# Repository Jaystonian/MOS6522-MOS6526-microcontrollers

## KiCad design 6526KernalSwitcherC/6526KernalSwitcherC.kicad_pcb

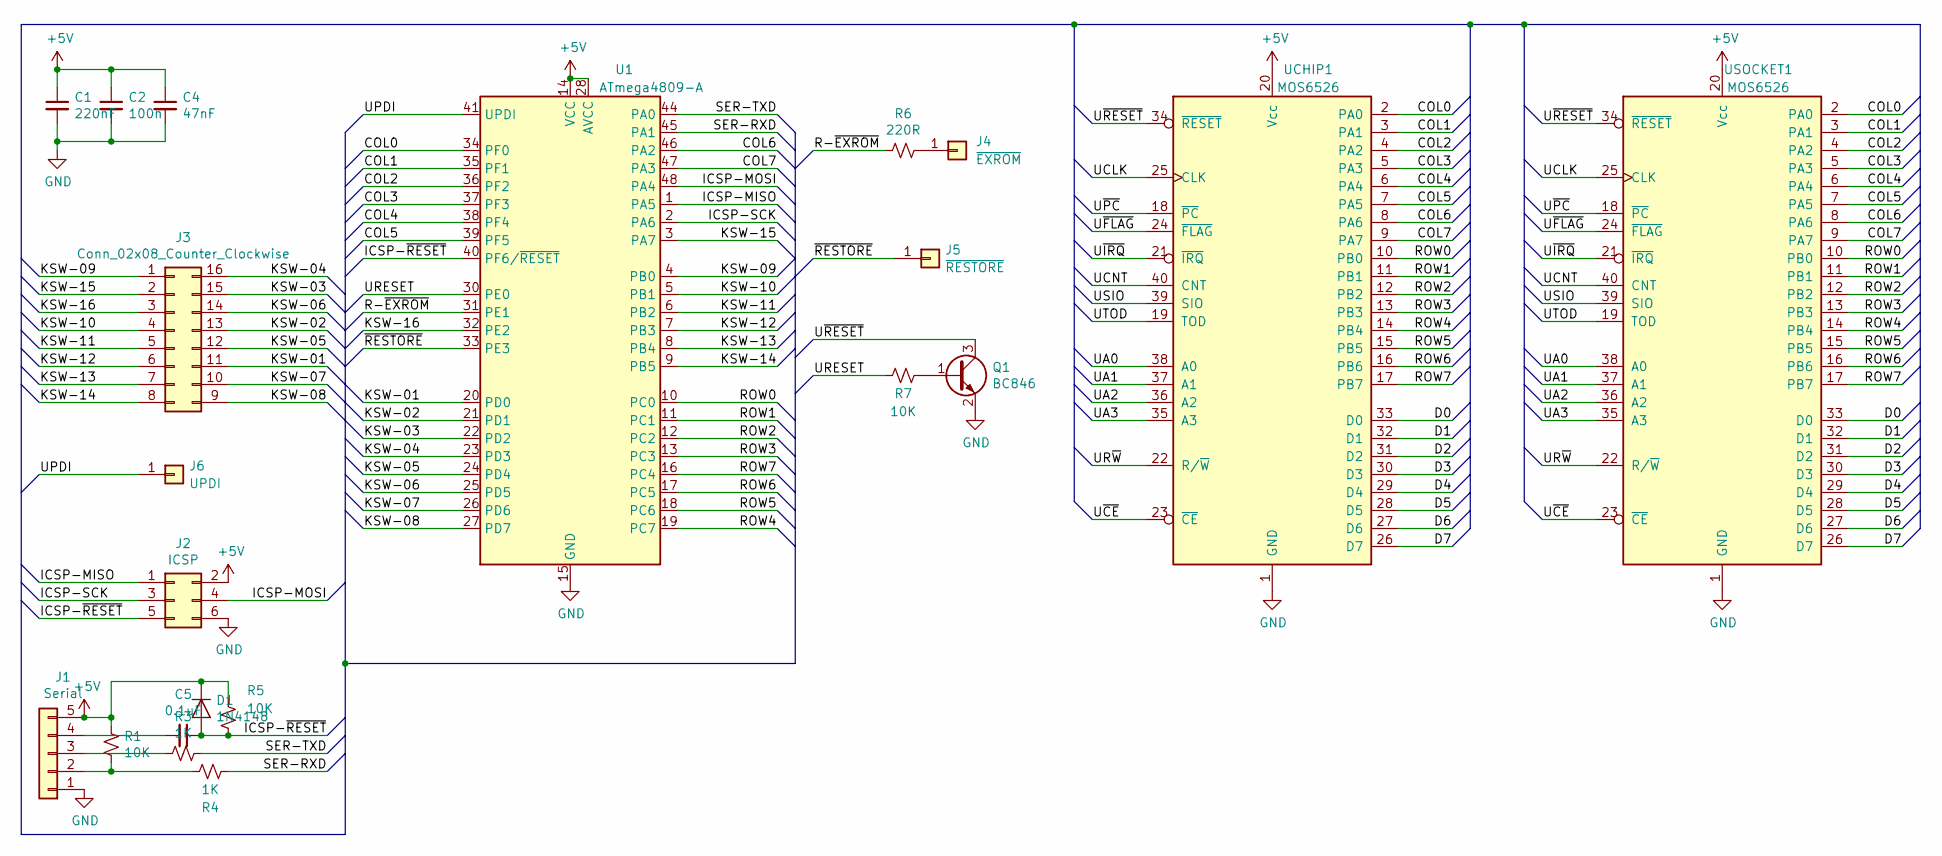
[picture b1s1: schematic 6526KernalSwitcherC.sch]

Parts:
C1: 220nF; C_0805_2012Metric_Pad1.15x1.40mm_HandSolder
C2: 100n; C_0805_2012Metric_Pad1.15x1.40mm_HandSolder
C4: 47nF; C_0805_2012Metric_Pad1.15x1.40mm_HandSolder
C5: 0.1uF; C_0805_2012Metric_Pad1.15x1.40mm_HandSolder
D1: 1N4148; D_MiniMELF
J1: Serial; PinHeader_1x05_P1.27mm_Vertical
J2: ICSP; PinHeader_2x03_P1.27mm_Vertical_SMD
J3: Conn_02x08_Counter_Clockwise; PinHeader_2x08_P2.00mm_Vertical
J4: ~EXROM; PinHeader_1x01_P2.54mm_Vertical
J5: ~RESTORE; PinHeader_1x01_P2.54mm_Vertical
J6: UPDI; PinHeader_1x01_P2.54mm_Vertical
Q1: BC846; SOT-23
R1, R5, R7: 10K; R_0805_2012Metric_Pad1.15x1.40mm_HandSolder
R3, R4: 1K; R_0805_2012Metric_Pad1.15x1.40mm_HandSolder
R6: 220R; R_0805_2012Metric_Pad1.15x1.40mm_HandSolder
U1: ATmega4809-A; TQFP-48_7x7mm_P0.5mm
UCHIP1: MOS6526; DIP-40_W15.24mm
USOCKET1: MOS6526; DIP-40_W15.24mm

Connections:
+5V: C1.1, C2.1, C4.1, D1.1 (K), J1.5, J2.2, R1.1, R5.1, U1.14 (VCC), U1.28 (AVCC), U1.42 (VCC), UCHIP1.20 (Vcc), USOCKET1.20 (Vcc)
/COL0: U1.34 (PF0), UCHIP1.2 (PA0), USOCKET1.2 (PA0)
/COL1: U1.35 (PF1), UCHIP1.3 (PA1), USOCKET1.3 (PA1)
/COL2: U1.36 (PF2), UCHIP1.4 (PA2), USOCKET1.4 (PA2)
/COL3: U1.37 (PF3), UCHIP1.5 (PA3), USOCKET1.5 (PA3)
/COL4: U1.38 (PF4), UCHIP1.6 (PA4), USOCKET1.6 (PA4)
/COL5: U1.39 (PF5), UCHIP1.7 (PA5), USOCKET1.7 (PA5)
/COL6: U1.46 (PA2), UCHIP1.8 (PA6), USOCKET1.8 (PA6)
/COL7: U1.47 (PA3), UCHIP1.9 (PA7), USOCKET1.9 (PA7)
/D0: UCHIP1.33 (D0), USOCKET1.33 (D0)
/D1: UCHIP1.32 (D1), USOCKET1.32 (D1)
/D2: UCHIP1.31 (D2), USOCKET1.31 (D2)
/D3: UCHIP1.30 (D3), USOCKET1.30 (D3)
/D4: UCHIP1.29 (D4), USOCKET1.29 (D4)
/D5: UCHIP1.28 (D5), USOCKET1.28 (D5)
/D6: UCHIP1.27 (D6), USOCKET1.27 (D6)
/D7: UCHIP1.26 (D7), USOCKET1.26 (D7)
/ICSP-MISO: J2.1, U1.1 (PA5)
/ICSP-MOSI: J2.4, U1.48 (PA4)
/ICSP-SCK: J2.3, U1.2 (PA6)
/ICSP-~RESET: C5.1, D1.2 (A), J2.5, R5.2, U1.40 (PF6/~RESET)
/KSW-01: J3.11, U1.20 (PD0)
/KSW-02: J3.13, U1.21 (PD1)
/KSW-03: J3.15, U1.22 (PD2)
/KSW-04: J3.16, U1.23 (PD3)
/KSW-05: J3.12, U1.24 (PD4)
/KSW-06: J3.14, U1.25 (PD5)
/KSW-07: J3.10, U1.26 (PD6)
/KSW-08: J3.9, U1.27 (PD7)
/KSW-09: J3.1, U1.4 (PB0)
/KSW-10: J3.4, U1.5 (PB1)
/KSW-11: J3.5, U1.6 (PB2)
/KSW-12: J3.6, U1.7 (PB3)
/KSW-13: J3.7, U1.8 (PB4)
/KSW-14: J3.8, U1.9 (PB5)
/KSW-15: J3.2, U1.3 (PA7)
/KSW-16: J3.3, U1.32 (PE2)
/R-~EXROM: R6.2, U1.31 (PE1)
/ROW0: U1.10 (PC0), UCHIP1.10 (PB0), USOCKET1.10 (PB0)
/ROW1: U1.11 (PC1), UCHIP1.11 (PB1), USOCKET1.11 (PB1)
/ROW2: U1.12 (PC2), UCHIP1.12 (PB2), USOCKET1.12 (PB2)
/ROW3: U1.13 (PC3), UCHIP1.13 (PB3), USOCKET1.13 (PB3)
/ROW4: U1.19 (PC7), UCHIP1.14 (PB4), USOCKET1.14 (PB4)
/ROW5: U1.18 (PC6), UCHIP1.15 (PB5), USOCKET1.15 (PB5)
/ROW6: U1.17 (PC5), UCHIP1.16 (PB6), USOCKET1.16 (PB6)
/ROW7: U1.16 (PC4), UCHIP1.17 (PB7), USOCKET1.17 (PB7)
/SER-RXD: R4.1, U1.45 (PA1)
/SER-TXD: R3.1, U1.44 (PA0)
/UA0: UCHIP1.38 (A0), USOCKET1.38 (A0)
/UA1: UCHIP1.37 (A1), USOCKET1.37 (A1)
/UA2: UCHIP1.36 (A2), USOCKET1.36 (A2)
/UA3: UCHIP1.35 (A3), USOCKET1.35 (A3)
/UCLK: UCHIP1.25 (CLK), USOCKET1.25 (CLK)
/UCNT: UCHIP1.40 (CNT), USOCKET1.40 (CNT)
/UPDI: J6.1, U1.41 (UPDI)
/URESET: R7.2, U1.30 (PE0)
/UR~W: UCHIP1.22 (R/~W~), USOCKET1.22 (R/~W~)
/USIO: UCHIP1.39 (SIO), USOCKET1.39 (SIO)
/UTOD: UCHIP1.19 (TOD), USOCKET1.19 (TOD)
/U~CE: UCHIP1.23 (~CE~), USOCKET1.23 (~CE~)
/U~FLAG: UCHIP1.24 (~FLAG~), USOCKET1.24 (~FLAG~)
/U~IRQ: UCHIP1.21 (~IRQ~), USOCKET1.21 (~IRQ~)
/U~PC: UCHIP1.18 (~PC~), USOCKET1.18 (~PC~)
/U~RESET: Q1.3 (C), UCHIP1.34 (~RESET~), USOCKET1.34 (~RESET~)
/~RESTORE: J5.1, U1.33 (PE3)
GND: C1.2, C2.2, C4.2, J1.1, J2.6, Q1.2 (E), U1.15 (GND), U1.29 (GND), U1.43 (GND), UCHIP1.1 (GND), USOCKET1.1 (GND)
unnamed: C5.2, J1.4
unnamed: J1.2, R1.2, R4.2
unnamed: J1.3, R3.2
unnamed: J4.1, R6.1
unnamed: Q1.1 (B), R7.1

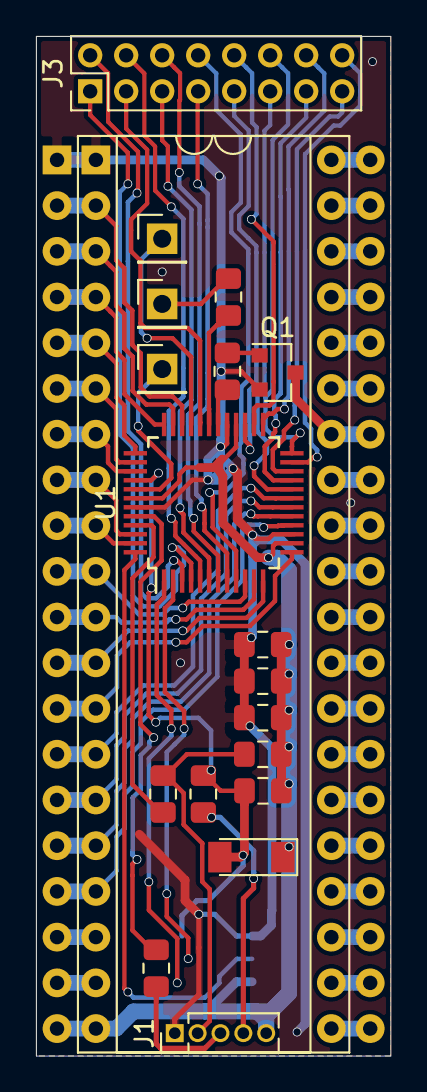
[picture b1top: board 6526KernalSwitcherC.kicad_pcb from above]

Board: 2 copper layers, 19.7 x 56.6 mm, 21 parts (1 on the bottom side), 71 nets.

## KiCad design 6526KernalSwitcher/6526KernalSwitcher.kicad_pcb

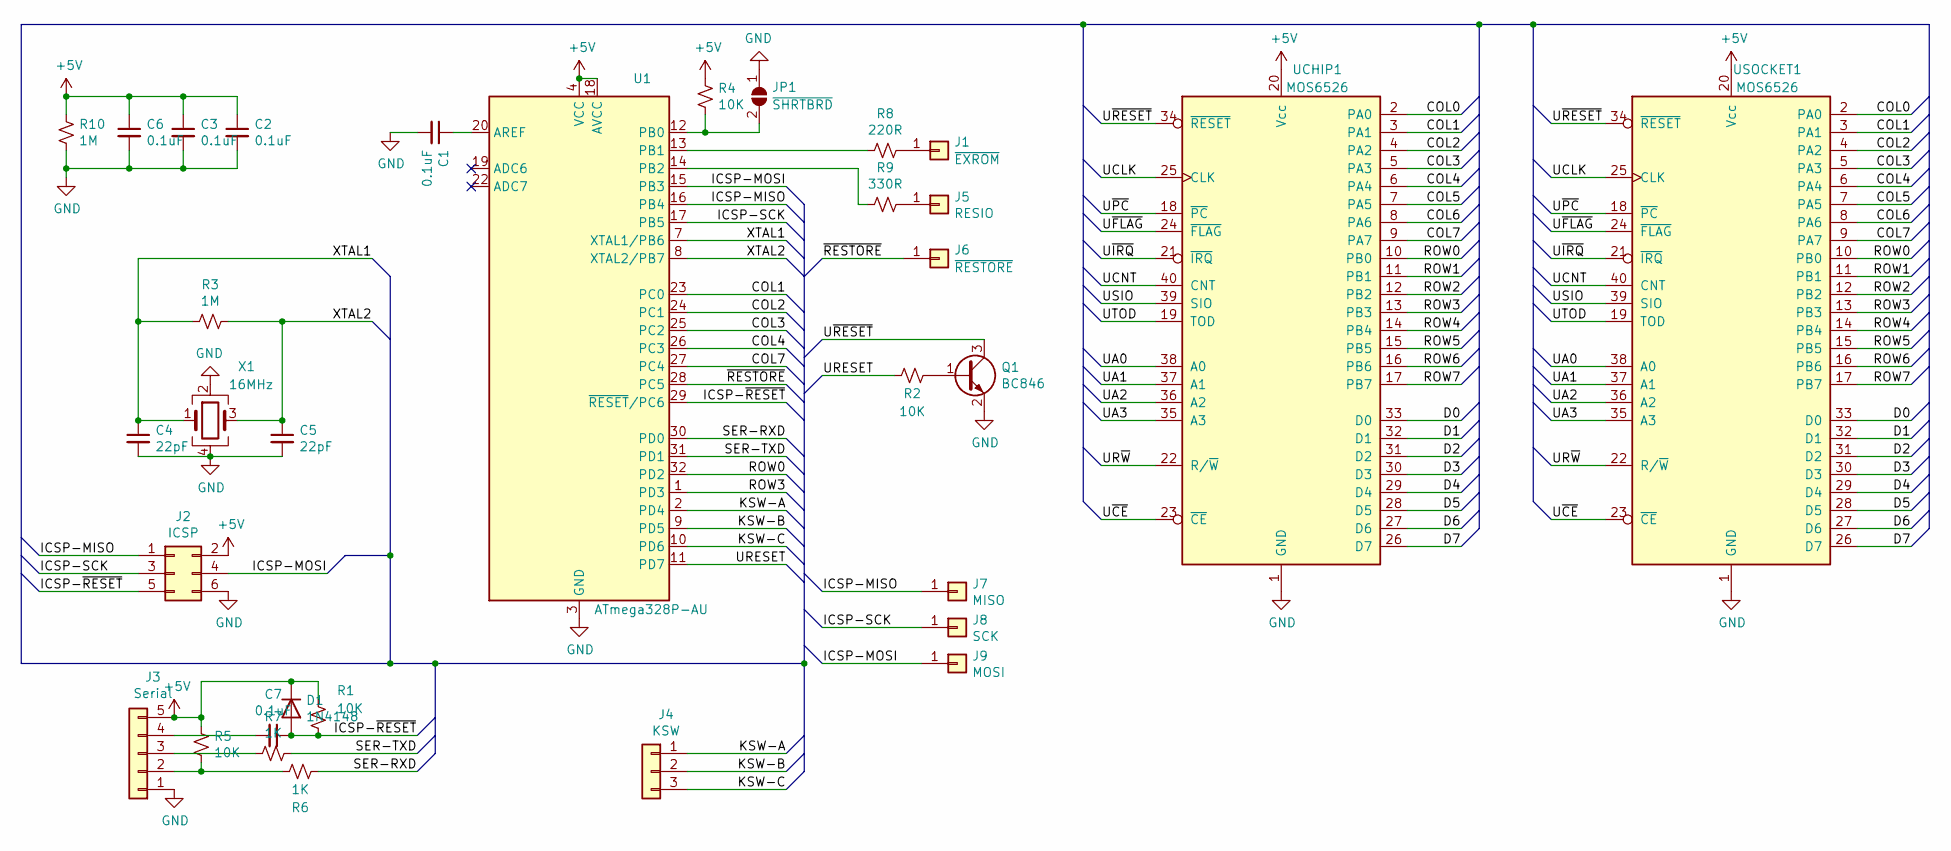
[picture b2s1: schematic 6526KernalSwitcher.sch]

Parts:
C1, C2, C3, C6, C7: 0.1uF; C_0805_2012Metric_Pad1.15x1.40mm_HandSolder
C4, C5: 22pF; C_0805_2012Metric_Pad1.15x1.40mm_HandSolder
D1: 1N4148; D_MiniMELF
J1: ~EXROM; PinHeader_1x01_P2.54mm_Vertical
J2: ICSP; PinHeader_2x03_P2.54mm_Vertical
J3: Serial; PinHeader_1x05_P2.54mm_Vertical
J4: KSW; PinHeader_1x03_P2.54mm_Vertical
J5: RESIO; PinHeader_1x01_P2.54mm_Vertical
J6: ~RESTORE; PinHeader_1x01_P2.54mm_Vertical
J7: MISO; SolderPad
J8: SCK; SolderPad
J9: MOSI; SolderPad
JP1: ~SHRTBRD; SolderJumper-2_P1.3mm_Open_RoundedPad1.0x1.5mm
Q1: BC846; SOT-23
R1, R2, R4, R5: 10K; R_0805_2012Metric_Pad1.15x1.40mm_HandSolder
R3, R10: 1M; R_0805_2012Metric_Pad1.15x1.40mm_HandSolder
R6, R7: 1K; R_0805_2012Metric_Pad1.15x1.40mm_HandSolder
R8: 220R; R_0805_2012Metric_Pad1.15x1.40mm_HandSolder
R9: 330R; R_0805_2012Metric_Pad1.15x1.40mm_HandSolder
U1: ATmega328P-AU; TQFP-32_7x7mm_P0.8mm
UCHIP1: MOS6526; DIP-40_W15.24mm
USOCKET1: MOS6526; DIP-40_W15.24mm
X1: 16MHz; Crystal_SMD_2016-4Pin_2.0x1.6mm

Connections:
+5V: C2.1, C3.1, C6.1, D1.1 (K), J2.2, J3.5, R1.1, R4.1, R5.1, R10.1, U1.4 (VCC), U1.6 (VCC), U1.18 (AVCC), UCHIP1.20 (Vcc), USOCKET1.20 (Vcc)
/COL0: UCHIP1.2 (PA0), USOCKET1.2 (PA0)
/COL1: U1.23 (PC0), UCHIP1.3 (PA1), USOCKET1.3 (PA1)
/COL2: U1.24 (PC1), UCHIP1.4 (PA2), USOCKET1.4 (PA2)
/COL3: U1.25 (PC2), UCHIP1.5 (PA3), USOCKET1.5 (PA3)
/COL4: U1.26 (PC3), UCHIP1.6 (PA4), USOCKET1.6 (PA4)
/COL5: UCHIP1.7 (PA5), USOCKET1.7 (PA5)
/COL6: UCHIP1.8 (PA6), USOCKET1.8 (PA6)
/COL7: U1.27 (PC4), UCHIP1.9 (PA7), USOCKET1.9 (PA7)
/D0: UCHIP1.33 (D0), USOCKET1.33 (D0)
/D1: UCHIP1.32 (D1), USOCKET1.32 (D1)
/D2: UCHIP1.31 (D2), USOCKET1.31 (D2)
/D3: UCHIP1.30 (D3), USOCKET1.30 (D3)
/D4: UCHIP1.29 (D4), USOCKET1.29 (D4)
/D5: UCHIP1.28 (D5), USOCKET1.28 (D5)
/D6: UCHIP1.27 (D6), USOCKET1.27 (D6)
/D7: UCHIP1.26 (D7), USOCKET1.26 (D7)
/ICSP-MISO: J2.1, J7.1, U1.16 (PB4)
/ICSP-MOSI: J2.4, J9.1, U1.15 (PB3)
/ICSP-SCK: J2.3, J8.1, U1.17 (PB5)
/ICSP-~RESET: C7.1, D1.2 (A), J2.5, R1.2, U1.29 (~RESET~/PC6)
/KSW-A: J4.1, U1.2 (PD4)
/KSW-B: J4.2, U1.9 (PD5)
/KSW-C: J4.3, U1.10 (PD6)
/ROW0: U1.32 (PD2), UCHIP1.10 (PB0), USOCKET1.10 (PB0)
/ROW1: UCHIP1.11 (PB1), USOCKET1.11 (PB1)
/ROW2: UCHIP1.12 (PB2), USOCKET1.12 (PB2)
/ROW3: U1.1 (PD3), UCHIP1.13 (PB3), USOCKET1.13 (PB3)
/ROW4: UCHIP1.14 (PB4), USOCKET1.14 (PB4)
/ROW5: UCHIP1.15 (PB5), USOCKET1.15 (PB5)
/ROW6: UCHIP1.16 (PB6), USOCKET1.16 (PB6)
/ROW7: UCHIP1.17 (PB7), USOCKET1.17 (PB7)
/SER-RXD: R6.1, U1.30 (PD0)
/SER-TXD: R7.1, U1.31 (PD1)
/UA0: UCHIP1.38 (A0), USOCKET1.38 (A0)
/UA1: UCHIP1.37 (A1), USOCKET1.37 (A1)
/UA2: UCHIP1.36 (A2), USOCKET1.36 (A2)
/UA3: UCHIP1.35 (A3), USOCKET1.35 (A3)
/UCLK: UCHIP1.25 (CLK), USOCKET1.25 (CLK)
/UCNT: UCHIP1.40 (CNT), USOCKET1.40 (CNT)
/URESET: R2.2, U1.11 (PD7)
/UR~W: UCHIP1.22 (R/~W~), USOCKET1.22 (R/~W~)
/USIO: UCHIP1.39 (SIO), USOCKET1.39 (SIO)
/UTOD: UCHIP1.19 (TOD), USOCKET1.19 (TOD)
/U~CE: UCHIP1.23 (~CE~), USOCKET1.23 (~CE~)
/U~FLAG: UCHIP1.24 (~FLAG~), USOCKET1.24 (~FLAG~)
/U~IRQ: UCHIP1.21 (~IRQ~), USOCKET1.21 (~IRQ~)
/U~PC: UCHIP1.18 (~PC~), USOCKET1.18 (~PC~)
/U~RESET: Q1.3 (C), UCHIP1.34 (~RESET~), USOCKET1.34 (~RESET~)
/XTAL1: C4.1, R3.2, U1.7 (XTAL1/PB6), X1.1
/XTAL2: C5.1, R3.1, U1.8 (XTAL2/PB7), X1.3
/~RESTORE: J6.1, U1.28 (PC5)
GND: C1.2, C2.2, C3.2, C4.2, C5.2, C6.2, J2.6, J3.1, JP1.1 (A), Q1.2 (E), R10.2, U1.3 (GND), U1.5 (GND), U1.21 (GND), UCHIP1.1 (GND), USOCKET1.1 (GND), X1.2, X1.4
unnamed: C1.1, U1.20 (AREF)
unnamed: C7.2, J3.4
unnamed: J1.1, R8.1
unnamed: J3.2, R5.2, R6.2
unnamed: J3.3, R7.2
unnamed: J5.1, R9.1
unnamed: JP1.2 (B), R4.2, U1.12 (PB0)
unnamed: Q1.1 (B), R2.1
unnamed: R8.2, U1.13 (PB1)
unnamed: R9.2, U1.14 (PB2)

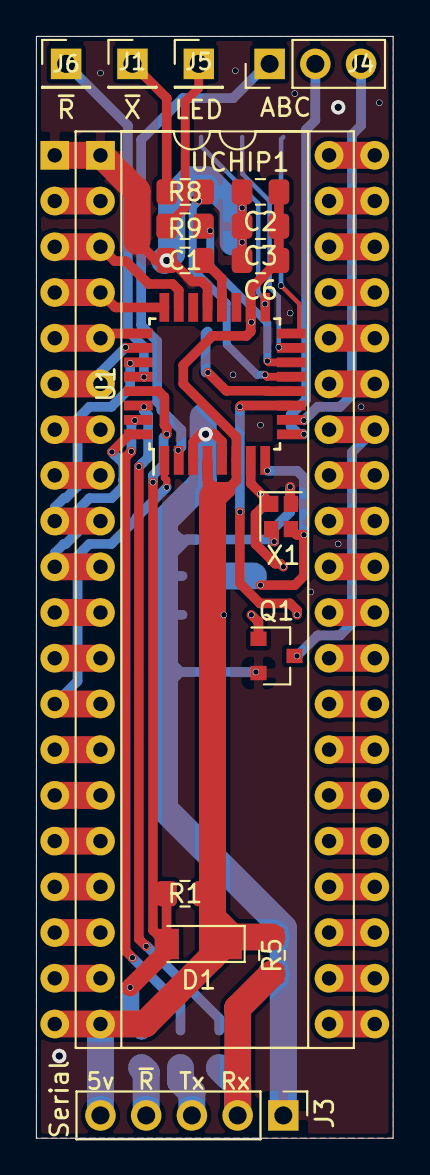
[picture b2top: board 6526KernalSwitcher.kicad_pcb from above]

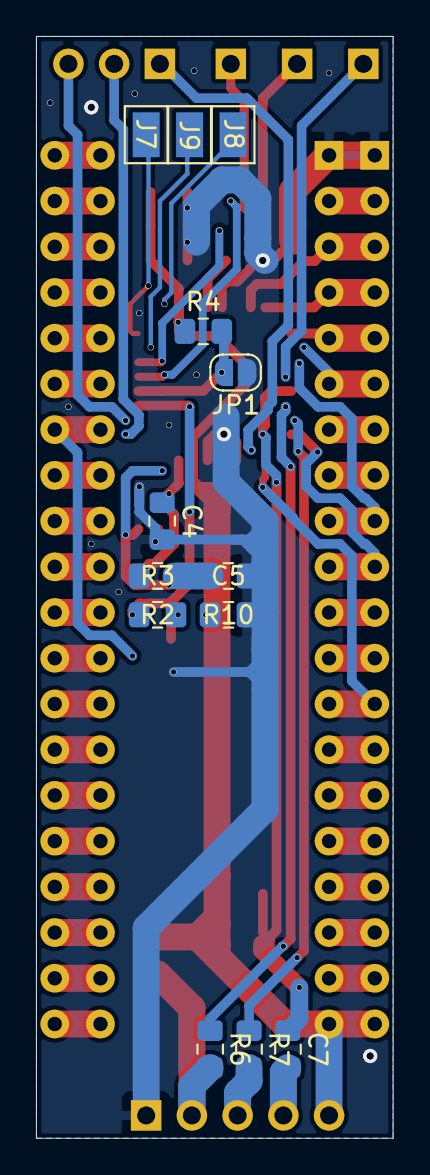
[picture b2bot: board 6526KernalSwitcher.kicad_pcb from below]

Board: 2 copper layers, 19.8 x 61.2 mm, 32 parts (13 on the bottom side), 63 nets.

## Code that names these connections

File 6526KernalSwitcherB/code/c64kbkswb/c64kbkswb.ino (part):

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const byte MAX_SELECT = 15; // For rotating output values (0-based, 0..15 = 16)
 
// C64 Keyboard Mapping
const int cnRow0 = _PD2;         // Row signal, input, active low, INT0
const int cnRow3 = _PD3;         // Row signal, input, active low, INT1
const int cnCol1 = _PC0;        // input, column signal, active low
const int cnCol2 = _PC1;        // input, column signal, active low
const int cnCol3 = _PC2;        // input, column signal, active low
const int cnCol4 = _PC3;        // input, column signal, active low
const int cnCol7 = _PC4;        // input, column signal, active low

// Selector Output
const int cnKSW_A = _PB1;
const int cnKSW_B = _PB0;
const int cnKSW_C = _PD7;
const int cnKSW_D = _PD6;
const int cnKSW_E = _PD5;

const int cnC64RESET = _PD4;     // output, RESET signal for the C64
const int cnRESTORE = _PC5;    // input, RESTORE key, active low
const int cnEXROM = _PB2;       // /EXROM Pin connected to pin header J4, pin 5 

const int cnRestoreCount = 2000; // count appr. 2 seconds for RestoreKey before Reset
const int cnExromCount = 3000;   // limit for EXROM reset
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
// variables
byte KAddr = 0;             // Address bits for selected Kernal
bool RestoreKey = 0;        // holds the info if the restore key is pressed 
bool oldRestoreKey = 0;     // remeber the old status to compare
int  countup = 0;           // counter for restore key time measurement
byte key = 128;             // calculate the Key
char buf[128];
bool bInc = false;
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
// Data Exchange variables for ISR (have to be volatile)
volatile bool NumPressed = 0;  // ISR flag for number pressed
volatile bool NumOdd = 0;      // ISR flag for odd numbers. Row0 => odd numbers, Row3 => even numbers
volatile byte ColData = 0x1F;  // column data

void setup() {
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          exrom_mode = 0;
        }
     }
     RestoreKey = 0;                      // in case the reading is HIGH, the Restore key is not pressed
     countup = 0;                         // restart the count down
  }
  else {
    RestoreKey = 1;                       // in case the restore is pressed, count up
    countup++;
    if (countup > cnExromCount) {          // time limit for EXROM reached?
       exrom_mode = 1;                    // activate EXROM mode
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
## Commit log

2021-10-18 Add files via upload
    from Sven's repo
2021-10-18 mega4809
